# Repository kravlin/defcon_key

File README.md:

# DEFCON 26 INFOBOOTH Key
## The Key to Misinformation

This is the Infobooth Key Badge for DEFCON 26. Created at the behest of Mello and Littlebruzer. 

## Bill of Materials

* [6mm square Buttons](https://www.adafruit.com/product/367) - I couldn't find this on mouser, and I needed 60 of them.
* [Coin Cell Battery Holder](https://www.mouser.com/ProductDetail/Eagle-Plastic-Devices/122-2520-GR?qs=sGAEpiMZZMtT9MhkajLHrsmOeam3f13HF0ge4CP9ILI%3d) - This stands off the board. This is good for me, but finding one without the standoffs would be good.
* [ATTINY84](https://www.mouser.com/ProductDetail/556-ATTINY84A-PU)
* [10K Pulldown Resistor](https://www.mouser.com/ProductDetail/603-MFR-25FRF5210K)
* [3mm Amber LEDs](https://www.mouser.com/ProductDetail/Vishay-Semiconductors/TLHE4600?qs=%2fjqivxn91ccKeAJQzr9uyA==)
* [5mm Red LEDs](https://www.mouser.com/ProductDetail/Kingbright/WP63SRD?qs=7QlcvZZejStVbcM3wnr71w==)
* [57.6ohm Resistor](https://www.mouser.com/ProductDetail/KOA-Speer/MF1-4DC57R6F?qs=sGAEpiMZZMsPqMdJzcrNwlJRvxcOW1fvRk6trFl%252b2HE=) - for the eye LEDs. Only 1 per badge.
* [110ohm Resistor](https://www.mouser.com/ProductDetail/603-MFR-25FBF52-110R) - 8 per badge. For amber LEDs
* CR2032 battery. Avalible...anywhere?

## Code

The code is fairly simple. it just creates a  bunch of cool animations. It was originally supposed to do game state, but the game didn't get finished before I had to make the badge happen, so I just dumped in the animations. There's a goal for DEFCON 27 to have the code re-finished and therefore be able to re-program everyone's badge with a game.

## Special Thanks

Mouse - for help with the pulldown resistor, as well as general cheerleadership :)

Mello - for running the Infobooth that i've been calling home the last 5 years.

Littlebruzer - for encouraging me to do this. I wouldn't probably have ever made this without your pushing me to work on it.

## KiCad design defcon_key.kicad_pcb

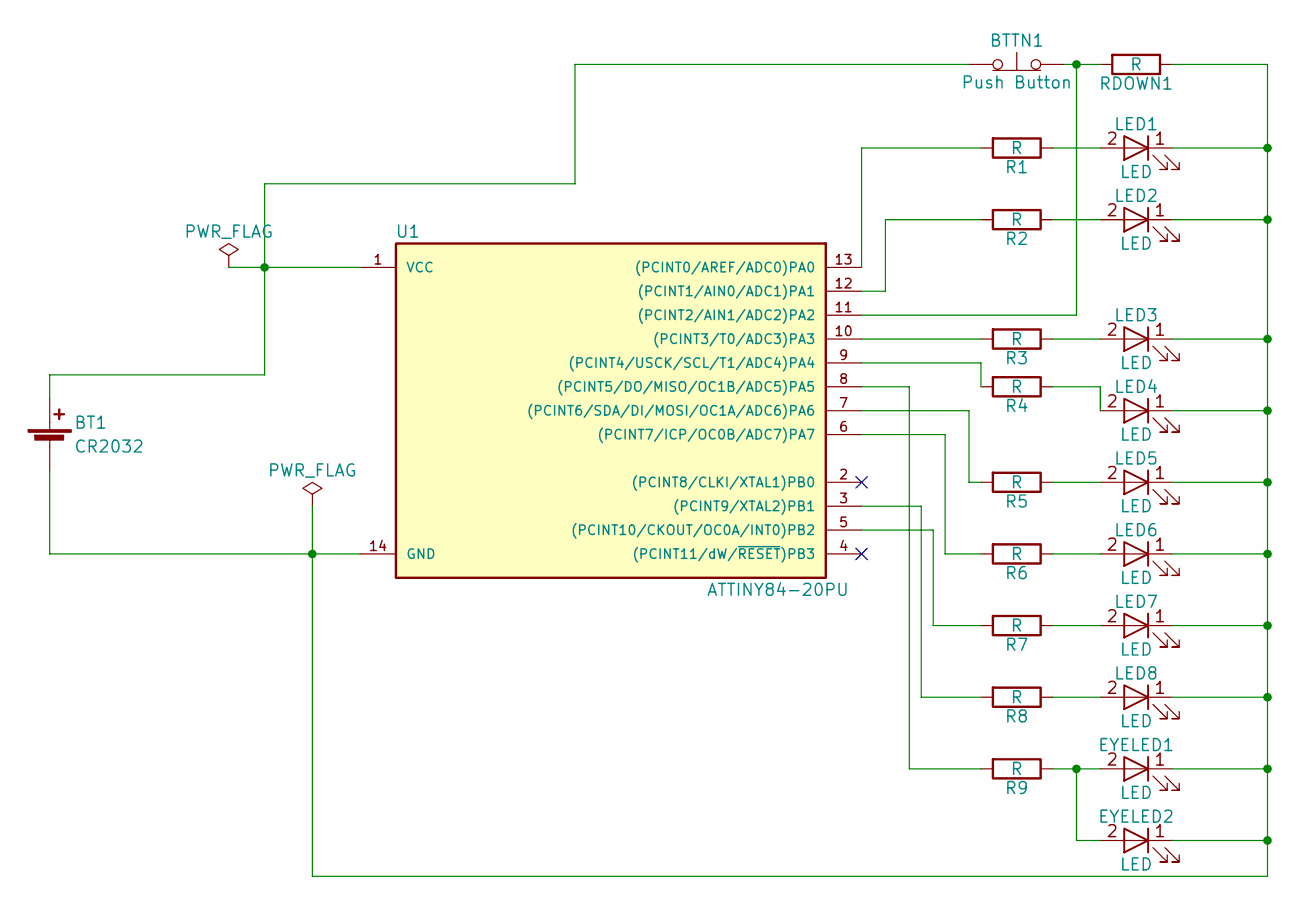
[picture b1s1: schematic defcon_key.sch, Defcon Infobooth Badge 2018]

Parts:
BT1: CR2032; Keystone_103_1x20mm-CoinCell
BTTN1: Push Button; SW_PUSH_6mm
EYELED1, EYELED2: LED; LED_D5.0mm
LED1, LED2, LED3, LED4, LED5, LED6, LED7, LED8: LED; LED_D3.0mm
R1, R2, R3, R4, R5, R6, R7, R8, R9: R; R_Axial_DIN0207_L6.3mm_D2.5mm_P7.62mm_Horizontal
RDOWN1: R; R_Axial_DIN0207_L6.3mm_D2.5mm_P7.62mm_Horizontal
U1: ATTINY84-20PU; DIP-14_W7.62mm

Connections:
unnamed: BT1.1 (+), BTTN1.1 (A), U1.1 (VCC)
unnamed: BT1.2 (-), EYELED1.1 (K), EYELED2.1 (K), LED1.1 (K), LED2.1 (K), LED3.1 (K), LED4.1 (K), LED5.1 (K), LED6.1 (K), LED7.1 (K), LED8.1 (K), RDOWN1.1, U1.14 (GND)
unnamed: BTTN1.2 (B), RDOWN1.2, U1.11 ((PCINT2/AIN1/ADC2)PA2)
unnamed: EYELED1.2 (A), EYELED2.2 (A), R9.1
unnamed: LED1.2 (A), R1.1
unnamed: LED2.2 (A), R2.1
unnamed: LED3.2 (A), R3.1
unnamed: LED4.2 (A), R4.1
unnamed: LED5.2 (A), R5.1
unnamed: LED6.2 (A), R6.1
unnamed: LED7.2 (A), R7.1
unnamed: LED8.2 (A), R8.1
unnamed: R1.2, U1.13 ((PCINT0/AREF/ADC0)PA0)
unnamed: R2.2, U1.12 ((PCINT1/AIN0/ADC1)PA1)
unnamed: R3.2, U1.10 ((PCINT3/T0/ADC3)PA3)
unnamed: R4.2, U1.9 ((PCINT4/USCK/SCL/T1/ADC4)PA4)
unnamed: R5.2, U1.7 ((PCINT6/SDA/DI/MOSI/OC1A/ADC6)PA6)
unnamed: R6.2, U1.6 ((PCINT7/ICP/OC0B/ADC7)PA7)
unnamed: R7.2, U1.5 ((PCINT10/CKOUT/OC0A/INT0)PB2)
unnamed: R8.2, U1.3 ((PCINT9/XTAL2)PB1)
unnamed: R9.2, U1.8 ((PCINT5/DO/MISO/OC1B/ADC5)PA5)

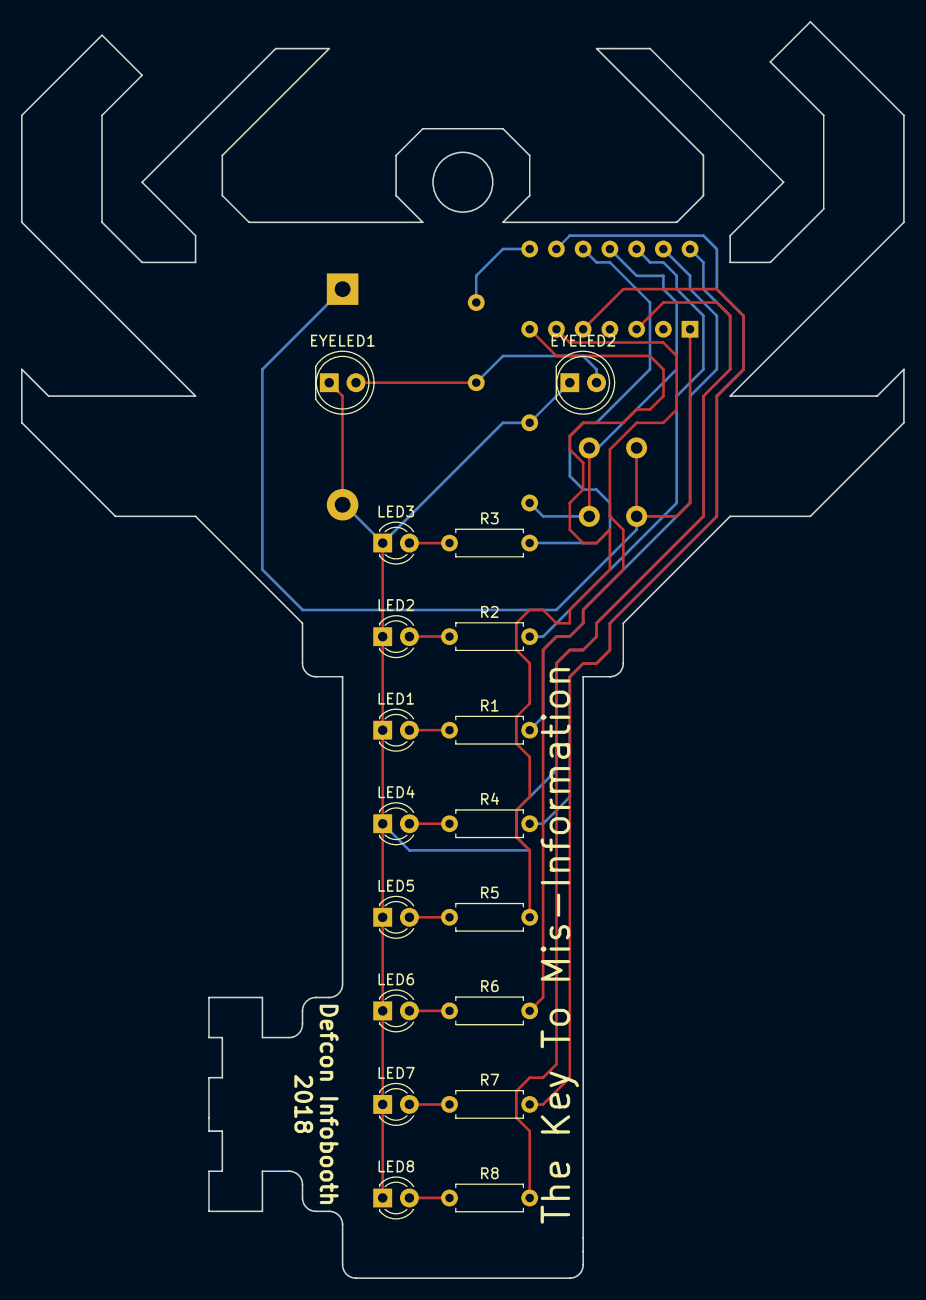
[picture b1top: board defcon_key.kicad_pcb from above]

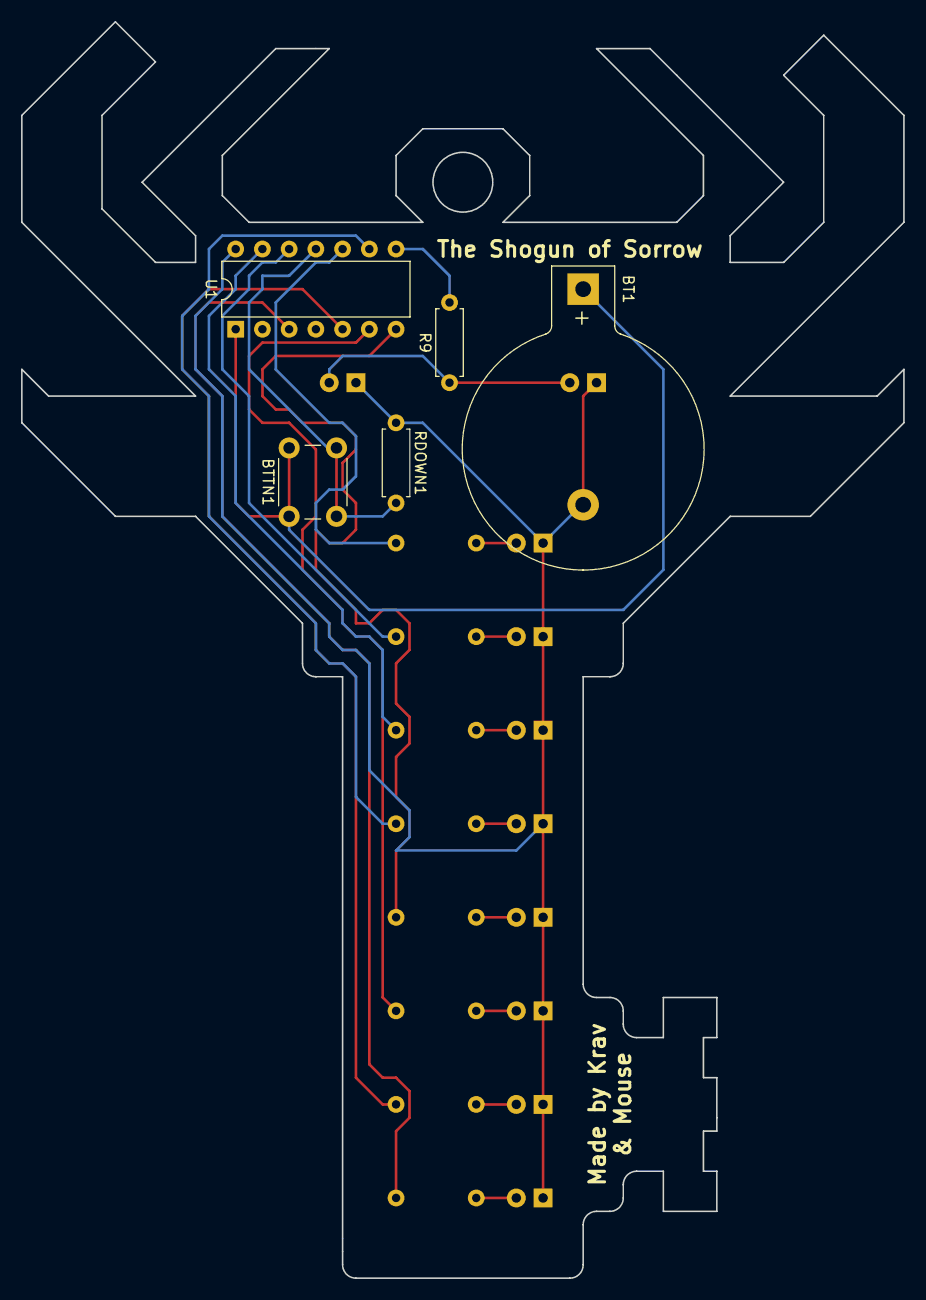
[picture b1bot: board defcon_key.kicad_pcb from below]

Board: 2 copper layers, 83.8 x 119.4 mm, 23 parts (5 on the bottom side), 21 nets.

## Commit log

2018-05-31 DESIGNS
2018-06-23 IMPROVEMENTS!
2018-07-10 Huge amount of code worked on. Need to push badge design upgrades.
2018-08-03 Updates!
2018-08-04 Tons of code
2018-08-15 v1.0 release
2018-08-15 Updated Readme for v1.0 release
